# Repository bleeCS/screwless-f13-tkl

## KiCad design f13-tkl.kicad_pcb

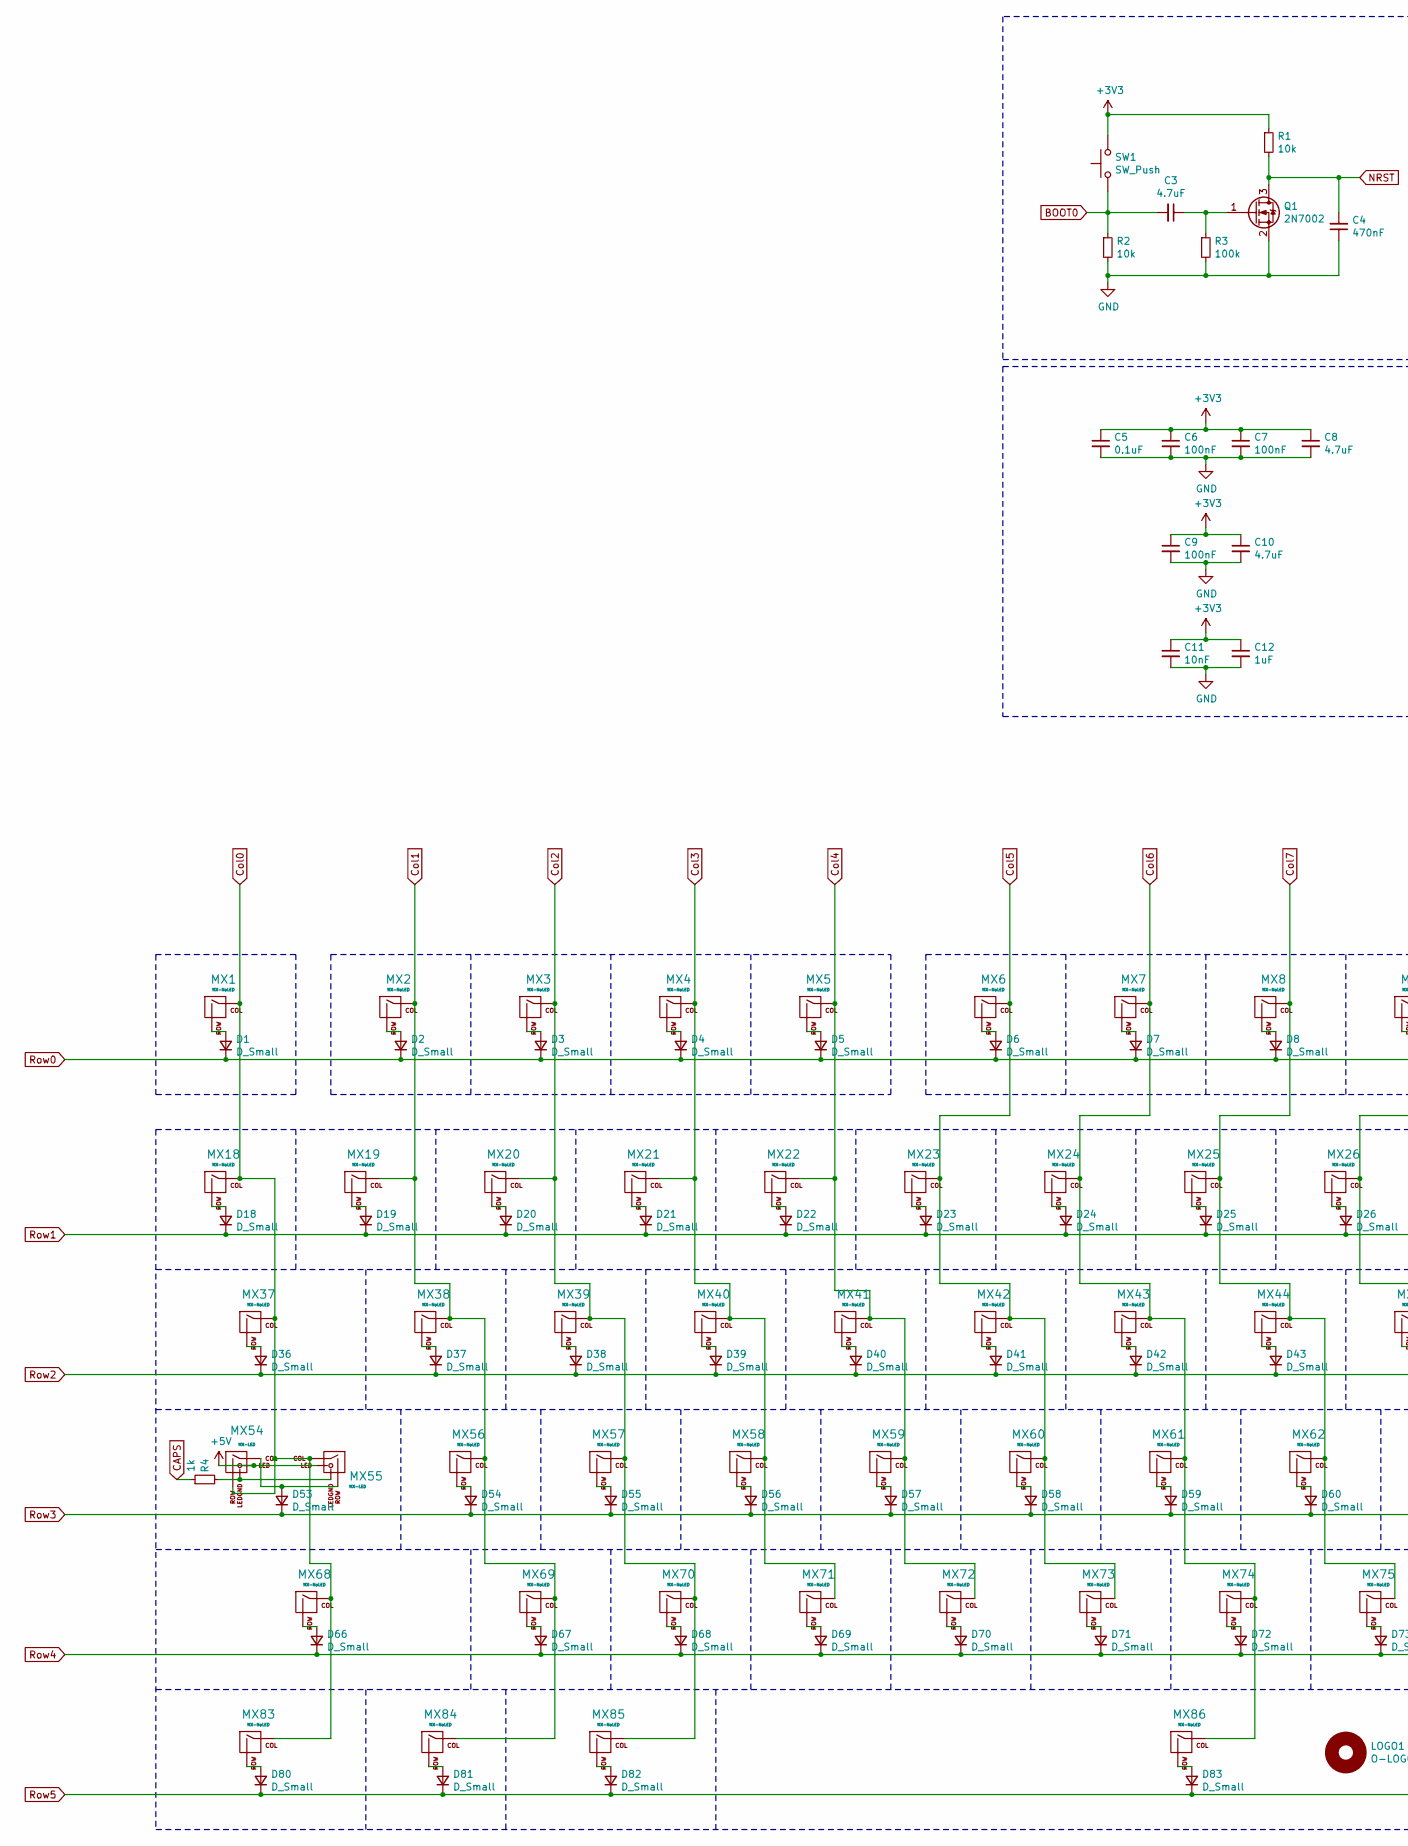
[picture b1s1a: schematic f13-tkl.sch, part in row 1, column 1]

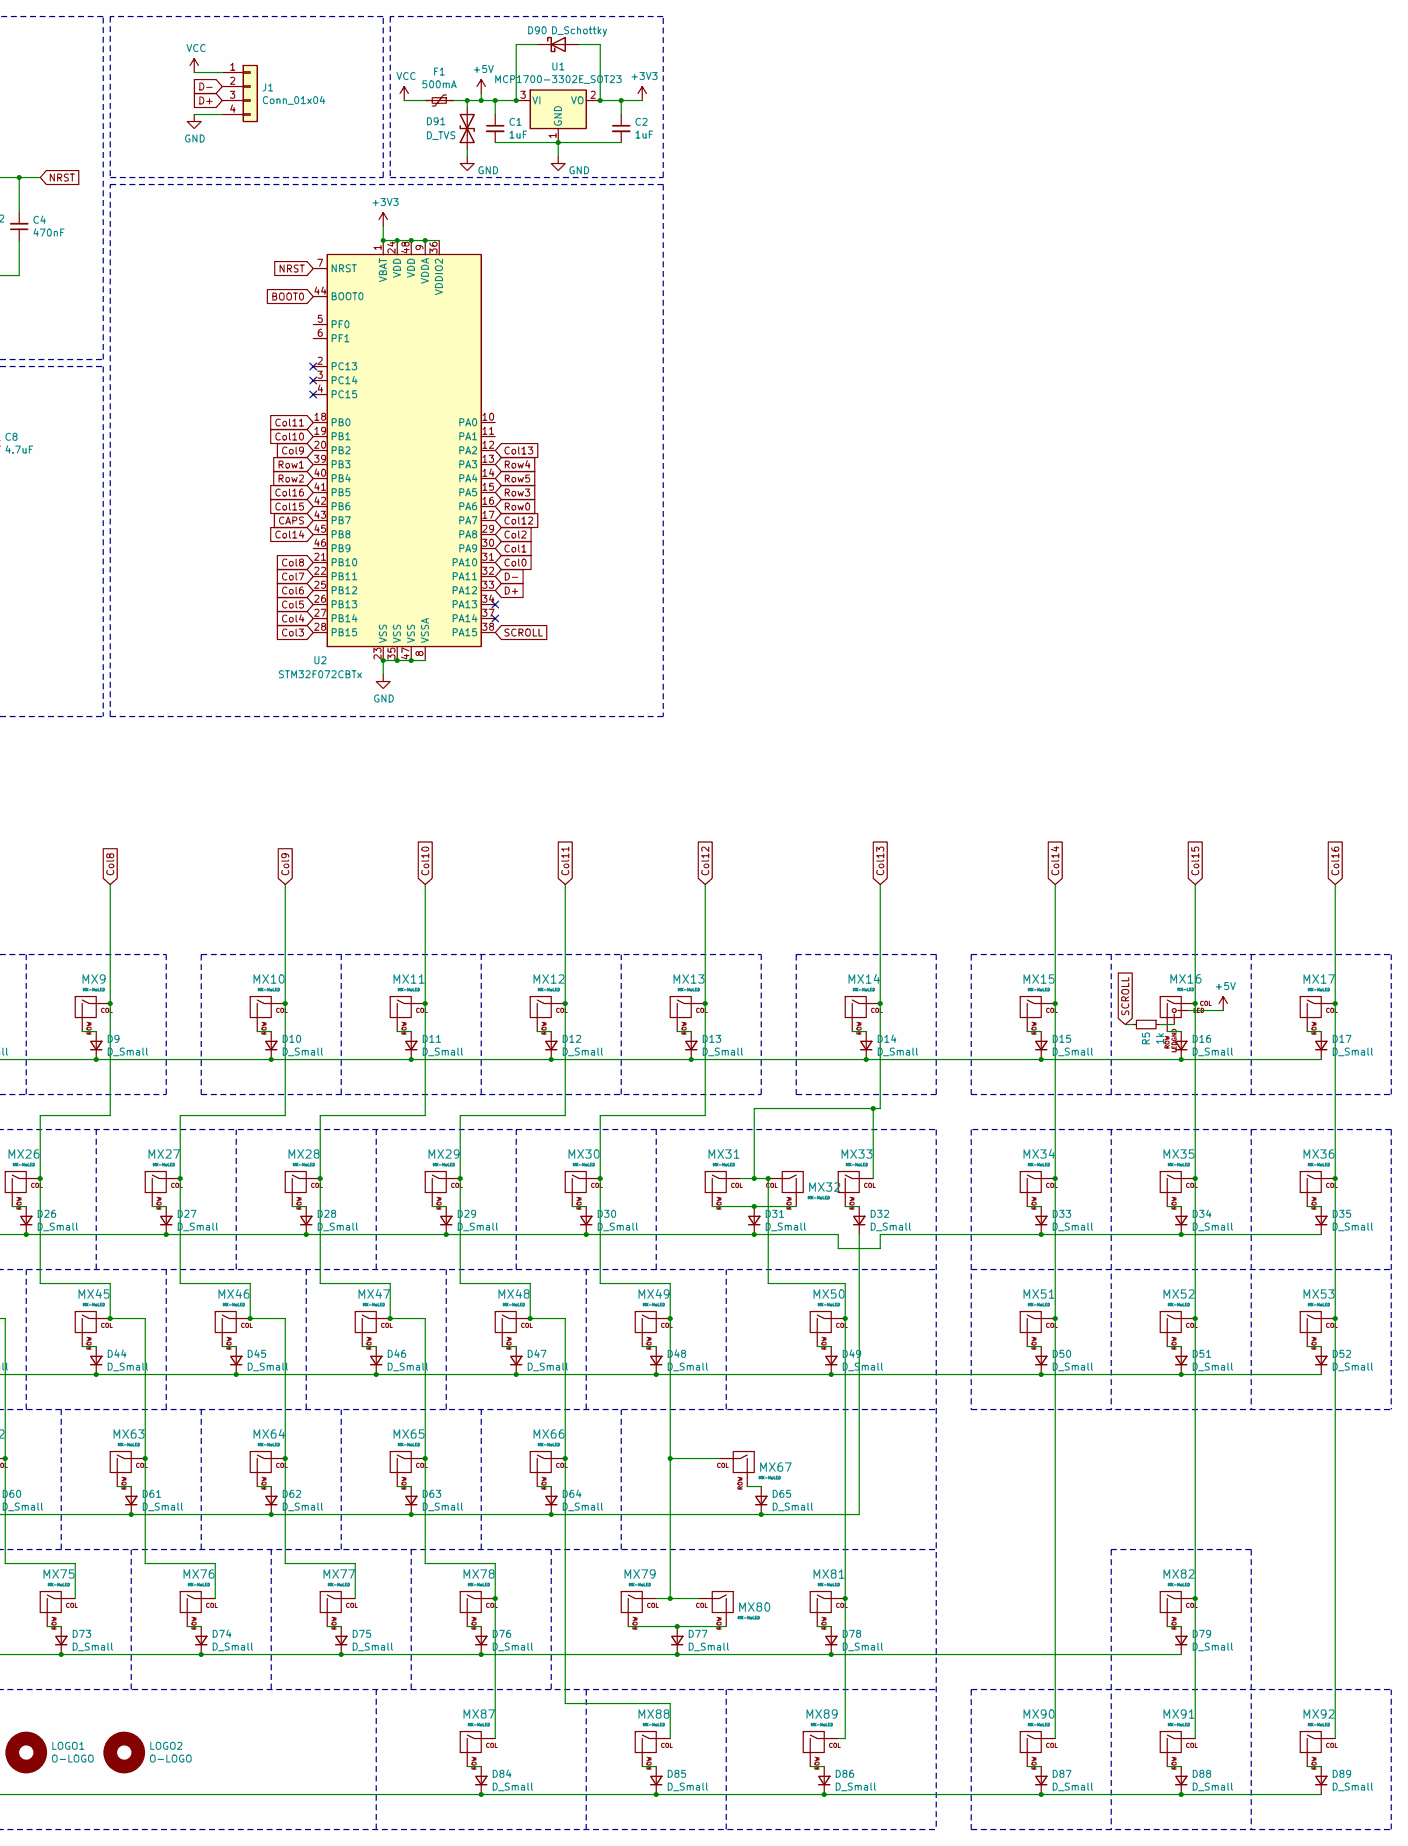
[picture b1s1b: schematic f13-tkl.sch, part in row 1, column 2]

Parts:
C1, C2, C12: 1uF; C_0603_1608Metric
C3, C8, C10: 4.7uF; C_0603_1608Metric
C4: 470nF; C_0603_1608Metric
C5: 0.1uF; C_0603_1608Metric
C6, C7, C9: 100nF; C_0603_1608Metric
C11: 10nF; C_0603_1608Metric
D1, D2, D3, D4, D5, D6, D7, D8, D9, D10, D11, D12, D13, D14, D15, D16, D17, D18, D19, D20, D21, D22, D23, D24, D25, D26, D27, D28, D29, D30, D31, D32, D33, D34, D35, D36, D37, D38, D39, D40, D41, D42, D43, D44, D45, D46, D47, D48, D49, D50, D51, D52, D53, D54, D55, D56, D57, D58, D59, D60, D61, D62, D63, D64, D65, D66, D67, D68, D69, D70, D71, D72, D73, D74, D75, D76, D77, D78, D79, D80, D81, D82, D83, D84, D85, D86, D87, D88, D89: D_Small; D_SOD-123
D90: D_Schottky; D_SOD-123
D91: D_TVS; D_SOD-123
F1: 500mA; Fuse_1206_3216Metric
J1: Conn_01x04; JST-SR-4
LOGO1, LOGO2: O-LOGO; o-logo-300dpi
MX1, MX2, MX3, MX4, MX5, MX6, MX7, MX8, MX9, MX10, MX11, MX12, MX13, MX14, MX15, MX17, MX18, MX19, MX20, MX21, MX22, MX23, MX24, MX25, MX26, MX27, MX28, MX29, MX30, MX31, MX33, MX34, MX35, MX36, MX38, MX39, MX40, MX41, MX42, MX43, MX44, MX45, MX46, MX47, MX48, MX49, MX51, MX52, MX53, MX56, MX57, MX58, MX59, MX60, MX61, MX62, MX63, MX64, MX65, MX66, MX69, MX70, MX71, MX72, MX73, MX74, MX75, MX76, MX77, MX78, MX81, MX82, MX84, MX88, MX90, MX91, MX92: MX-NoLED; MXOnly-1U-NoLED
MX16: MX-LED; MXOnly-1U
MX32: MX-NoLED; MXOnly-2U-NoLED
MX37, MX50, MX83, MX85, MX87, MX89: MX-NoLED; MXOnly-1.5U-NoLED
MX54: MX-LED; MXOnly-1.25U-FLIPPED
MX55: MX-LED; MXOnly-1.75U
MX67: MX-NoLED; MXOnly-2.25U-ReversedStabilizers-NoLED
MX68: MX-NoLED; MXOnly-2.25U-NoLED
MX79: MX-NoLED; MXOnly-1.75U-NoLED
MX80: MX-NoLED; MXOnly-2.75U-NoLED
MX86: MX-NoLED; MXOnly-7U-ReversedStabilizers-NoLED
Q1: 2N7002; SOT-23
R1, R2: 10k; R_0603_1608Metric
R3: 100k; R_0603_1608Metric
R4, R5: 1k; R_0603_1608Metric
SW1: SW_Push; K2-1187SQ-A4SW-06
U1: MCP1700-3302E_SOT23; SOT-23
U2: STM32F072CBTx; LQFP-48_7x7mm_P0.5mm

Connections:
+3V3: C2.1, C5.1, C6.1, C7.1, C8.1, C9.1, C10.1, C11.1, C12.1, D90.2 (A), R1.1, SW1.2, U1.2 (VO), U2.1 (VBAT), U2.9 (VDDA), U2.24 (VDD), U2.36 (VDDIO2), U2.48 (VDD)
+5V: C1.1, D90.1 (K), D91.2 (A2), F1.1, MX16.3 (LED), MX54.3 (LED), MX55.3 (LED), U1.3 (VI)
BOOT0: C3.2, R2.1, SW1.1, U2.44 (BOOT0)
CAPS: R4.1, U2.43 (PB7)
Col0: MX1.1 (COL), MX18.1 (COL), MX37.1 (COL), MX54.2 (ROW), MX55.1 (COL), MX68.1 (COL), MX83.1 (COL), U2.31 (PA10)
Col1: MX2.1 (COL), MX19.1 (COL), MX38.1 (COL), MX56.1 (COL), MX69.1 (COL), MX84.1 (COL), U2.30 (PA9)
Col2: MX3.1 (COL), MX20.1 (COL), MX39.1 (COL), MX57.1 (COL), MX70.1 (COL), MX85.1 (COL), U2.29 (PA8)
Col3: MX4.1 (COL), MX21.1 (COL), MX40.1 (COL), MX58.1 (COL), MX71.1 (COL), U2.28 (PB15)
Col4: MX5.1 (COL), MX22.1 (COL), MX41.1 (COL), MX59.1 (COL), MX72.1 (COL), U2.27 (PB14)
Col5: MX6.1 (COL), MX23.1 (COL), MX42.1 (COL), MX60.1 (COL), MX73.1 (COL), U2.26 (PB13)
Col6: MX7.1 (COL), MX24.1 (COL), MX43.1 (COL), MX61.1 (COL), MX74.1 (COL), MX86.1 (COL), U2.25 (PB12)
Col7: MX8.1 (COL), MX25.1 (COL), MX44.1 (COL), MX62.1 (COL), MX75.1 (COL), U2.22 (PB11)
Col8: MX9.1 (COL), MX26.1 (COL), MX45.1 (COL), MX63.1 (COL), MX76.1 (COL), U2.21 (PB10)
Col9: MX10.1 (COL), MX27.1 (COL), MX46.1 (COL), MX64.1 (COL), MX77.1 (COL), U2.20 (PB2)
Col10: MX11.1 (COL), MX28.1 (COL), MX47.1 (COL), MX65.1 (COL), MX78.1 (COL), MX87.1 (COL), U2.19 (PB1)
Col11: MX12.1 (COL), MX29.1 (COL), MX48.1 (COL), MX66.1 (COL), MX88.1 (COL), U2.18 (PB0)
Col12: MX13.1 (COL), MX30.1 (COL), MX49.1 (COL), MX67.1 (COL), MX79.1 (COL), MX80.1 (COL), U2.17 (PA7)
Col13: MX14.1 (COL), MX31.1 (COL), MX32.1 (COL), MX33.1 (COL), MX50.1 (COL), MX81.1 (COL), MX89.1 (COL), U2.12 (PA2)
Col14: MX15.1 (COL), MX34.1 (COL), MX51.1 (COL), MX90.1 (COL), U2.45 (PB8)
Col15: MX16.1 (COL), MX35.1 (COL), MX52.1 (COL), MX82.1 (COL), MX91.1 (COL), U2.42 (PB6)
Col16: MX17.1 (COL), MX36.1 (COL), MX53.1 (COL), MX92.1 (COL), U2.41 (PB5)
D+: J1.3, U2.33 (PA12)
D-: J1.2, U2.32 (PA11)
GND: C1.2, C2.2, C4.1, C5.2, C6.2, C7.2, C8.2, C9.2, C10.2, C11.2, C12.2, D91.1 (A1), J1.4, Q1.2 (S), R2.2, R3.2, U1.1 (GND), U2.8 (VSSA), U2.23 (VSS), U2.35 (VSS), U2.47 (VSS)
NRST: C4.2, Q1.3 (D), R1.2, U2.7 (NRST)
unnamed: C3.1, Q1.1 (G), R3.1
unnamed: D1.2 (A), MX1.2 (ROW)
unnamed: D2.2 (A), MX2.2 (ROW)
unnamed: D3.2 (A), MX3.2 (ROW)
unnamed: D4.2 (A), MX4.2 (ROW)
unnamed: D5.2 (A), MX5.2 (ROW)
unnamed: D6.2 (A), MX6.2 (ROW)
unnamed: D7.2 (A), MX7.2 (ROW)
unnamed: D8.2 (A), MX8.2 (ROW)
unnamed: D9.2 (A), MX9.2 (ROW)
unnamed: D10.2 (A), MX10.2 (ROW)
unnamed: D11.2 (A), MX11.2 (ROW)
unnamed: D12.2 (A), MX12.2 (ROW)
unnamed: D13.2 (A), MX13.2 (ROW)
unnamed: D14.2 (A), MX14.2 (ROW)
unnamed: D15.2 (A), MX15.2 (ROW)
unnamed: D16.2 (A), MX16.2 (ROW)
unnamed: D17.2 (A), MX17.2 (ROW)
unnamed: D18.2 (A), MX18.2 (ROW)
unnamed: D19.2 (A), MX19.2 (ROW)
unnamed: D20.2 (A), MX20.2 (ROW)
unnamed: D21.2 (A), MX21.2 (ROW)
unnamed: D22.2 (A), MX22.2 (ROW)
unnamed: D23.2 (A), MX23.2 (ROW)
unnamed: D24.2 (A), MX24.2 (ROW)
unnamed: D25.2 (A), MX25.2 (ROW)
unnamed: D26.2 (A), MX26.2 (ROW)
unnamed: D27.2 (A), MX27.2 (ROW)
unnamed: D28.2 (A), MX28.2 (ROW)
unnamed: D29.2 (A), MX29.2 (ROW)
unnamed: D30.2 (A), MX30.2 (ROW)
unnamed: D31.2 (A), MX31.2 (ROW), MX32.2 (ROW)
unnamed: D32.2 (A), MX33.2 (ROW)
unnamed: D33.2 (A), MX34.2 (ROW)
unnamed: D34.2 (A), MX35.2 (ROW)
unnamed: D35.2 (A), MX36.2 (ROW)
unnamed: D36.2 (A), MX37.2 (ROW)
unnamed: D37.2 (A), MX38.2 (ROW)
unnamed: D38.2 (A), MX39.2 (ROW)
unnamed: D39.2 (A), MX40.2 (ROW)
unnamed: D40.2 (A), MX41.2 (ROW)
unnamed: D41.2 (A), MX42.2 (ROW)
unnamed: D42.2 (A), MX43.2 (ROW)
unnamed: D43.2 (A), MX44.2 (ROW)
unnamed: D44.2 (A), MX45.2 (ROW)
unnamed: D45.2 (A), MX46.2 (ROW)
unnamed: D46.2 (A), MX47.2 (ROW)
unnamed: D47.2 (A), MX48.2 (ROW)
unnamed: D48.2 (A), MX49.2 (ROW)
unnamed: D49.2 (A), MX50.2 (ROW)
unnamed: D50.2 (A), MX51.2 (ROW)
unnamed: D51.2 (A), MX52.2 (ROW)
unnamed: D52.2 (A), MX53.2 (ROW)
unnamed: D53.2 (A), MX54.1 (COL), MX55.2 (ROW)
unnamed: D54.2 (A), MX56.2 (ROW)
unnamed: D55.2 (A), MX57.2 (ROW)
unnamed: D56.2 (A), MX58.2 (ROW)
unnamed: D57.2 (A), MX59.2 (ROW)
unnamed: D58.2 (A), MX60.2 (ROW)
unnamed: D59.2 (A), MX61.2 (ROW)
unnamed: D60.2 (A), MX62.2 (ROW)
unnamed: D61.2 (A), MX63.2 (ROW)
unnamed: D62.2 (A), MX64.2 (ROW)
unnamed: D63.2 (A), MX65.2 (ROW)
unnamed: D64.2 (A), MX66.2 (ROW)
unnamed: D65.2 (A), MX67.2 (ROW)
unnamed: D66.2 (A), MX68.2 (ROW)
unnamed: D67.2 (A), MX69.2 (ROW)
unnamed: D68.2 (A), MX70.2 (ROW)
unnamed: D69.2 (A), MX71.2 (ROW)
unnamed: D70.2 (A), MX72.2 (ROW)
unnamed: D71.2 (A), MX73.2 (ROW)
unnamed: D72.2 (A), MX74.2 (ROW)
unnamed: D73.2 (A), MX75.2 (ROW)
unnamed: D74.2 (A), MX76.2 (ROW)
unnamed: D75.2 (A), MX77.2 (ROW)
unnamed: D76.2 (A), MX78.2 (ROW)
unnamed: D77.2 (A), MX79.2 (ROW), MX80.2 (ROW)
unnamed: D78.2 (A), MX81.2 (ROW)
unnamed: D79.2 (A), MX82.2 (ROW)
unnamed: D80.2 (A), MX83.2 (ROW)
unnamed: D81.2 (A), MX84.2 (ROW)
unnamed: D82.2 (A), MX85.2 (ROW)
unnamed: D83.2 (A), MX86.2 (ROW)
unnamed: D84.2 (A), MX87.2 (ROW)
unnamed: D85.2 (A), MX88.2 (ROW)
unnamed: D86.2 (A), MX89.2 (ROW)
unnamed: D87.2 (A), MX90.2 (ROW)
unnamed: D88.2 (A), MX91.2 (ROW)
unnamed: D89.2 (A), MX92.2 (ROW)
unnamed: MX16.4 (LEDGND), R5.1
unnamed: MX54.4 (LEDGND), MX55.4 (LEDGND), R4.2
Row0: D1.1 (K), D2.1 (K), D3.1 (K), D4.1 (K), D5.1 (K), D6.1 (K), D7.1 (K), D8.1 (K), D9.1 (K), D10.1 (K), D11.1 (K), D12.1 (K), D13.1 (K), D14.1 (K), D15.1 (K), D16.1 (K), D17.1 (K), U2.16 (PA6)
Row1: D18.1 (K), D19.1 (K), D20.1 (K), D21.1 (K), D22.1 (K), D23.1 (K), D24.1 (K), D25.1 (K), D26.1 (K), D27.1 (K), D28.1 (K), D29.1 (K), D30.1 (K), D31.1 (K), D33.1 (K), D34.1 (K), D35.1 (K), U2.39 (PB3)
Row2: D36.1 (K), D37.1 (K), D38.1 (K), D39.1 (K), D40.1 (K), D41.1 (K), D42.1 (K), D43.1 (K), D44.1 (K), D45.1 (K), D46.1 (K), D47.1 (K), D48.1 (K), D49.1 (K), D50.1 (K), D51.1 (K), D52.1 (K), U2.40 (PB4)
Row3: D32.1 (K), D53.1 (K), D54.1 (K), D55.1 (K), D56.1 (K), D57.1 (K), D58.1 (K), D59.1 (K), D60.1 (K), D61.1 (K), D62.1 (K), D63.1 (K), D64.1 (K), D65.1 (K), U2.15 (PA5)
Row4: D66.1 (K), D67.1 (K), D68.1 (K), D69.1 (K), D70.1 (K), D71.1 (K), D72.1 (K), D73.1 (K), D74.1 (K), D75.1 (K), D76.1 (K), D77.1 (K), D78.1 (K), D79.1 (K), U2.13 (PA3)
Row5: D80.1 (K), D81.1 (K), D82.1 (K), D83.1 (K), D84.1 (K), D85.1 (K), D86.1 (K), D87.1 (K), D88.1 (K), D89.1 (K), U2.14 (PA4)
SCROLL: R5.2, U2.38 (PA15)
VCC: F1.2, J1.1

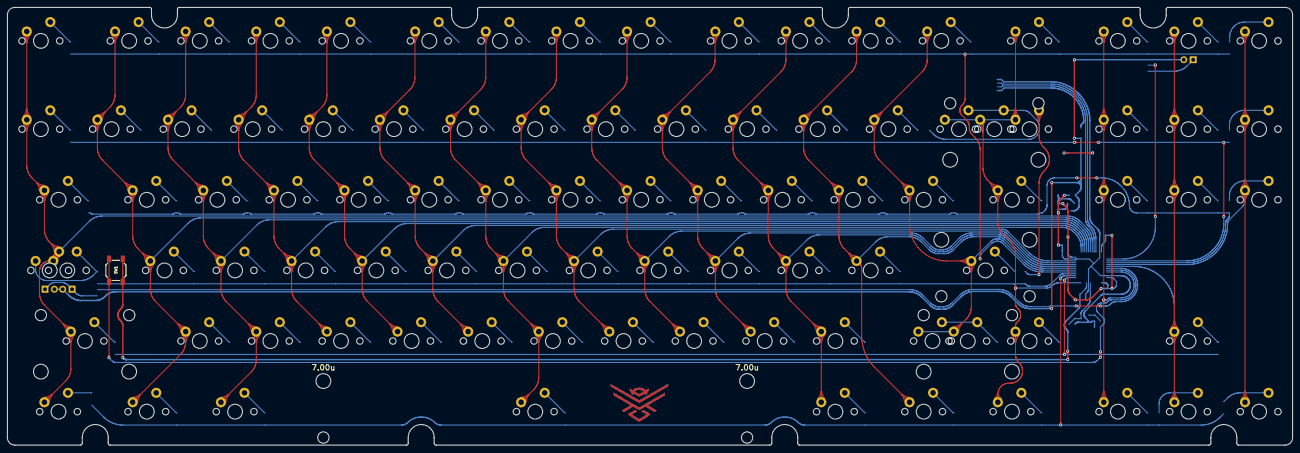
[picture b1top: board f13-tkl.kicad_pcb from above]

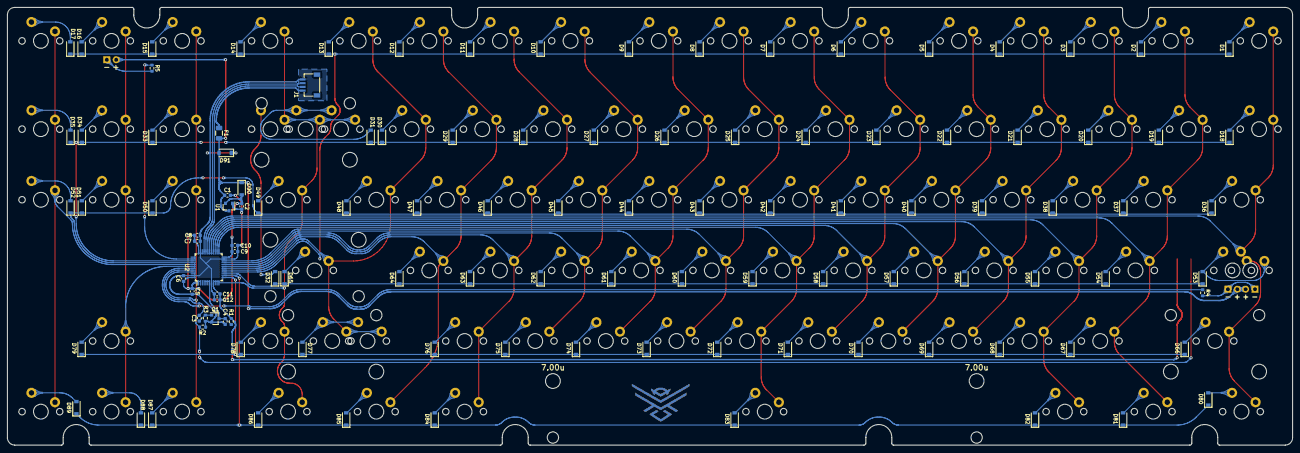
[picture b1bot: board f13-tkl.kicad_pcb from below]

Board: 2 copper layers, 346.7 x 118.1 mm, 208 parts (114 on the bottom side), 125 nets.

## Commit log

2020-12-26 initialize project and add submodules
2020-12-26 changes to submodules
2020-12-26 boot/reset, decoupling caps, voltage reg, jst connector, place mcu
2020-12-26 finish schematic rev1
2020-12-27 preliminary component placement, update submodule
2021-01-10 lots of changes
